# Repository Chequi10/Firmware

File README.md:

# Firmware
Tendra la funcion de controlar los 2 canales CAN, y se comunicara con la pc mendiente puerto Serie

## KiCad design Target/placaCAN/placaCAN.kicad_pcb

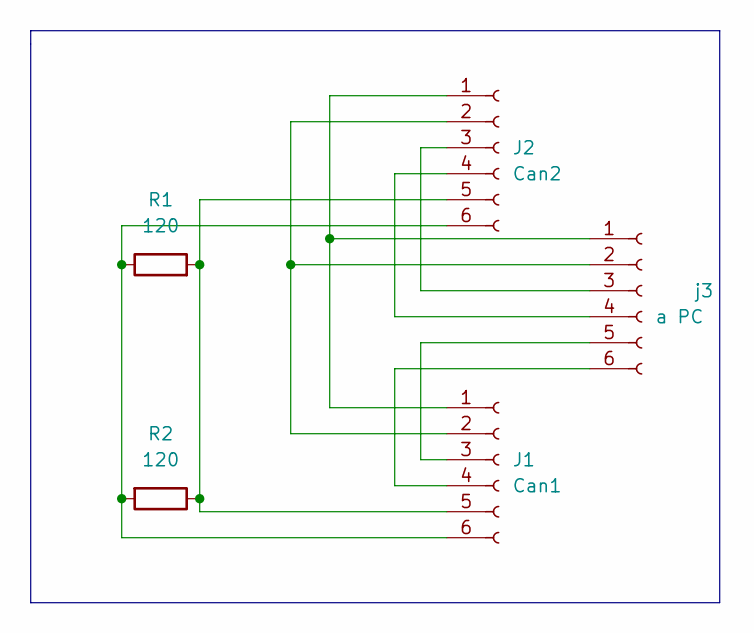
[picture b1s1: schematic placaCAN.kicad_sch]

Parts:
J1: Can1; R_Array_SIP6
J2: Can2; R_Array_SIP6
R1, R2: 120; R_Box_L13.0mm_W4.0mm_P9.00mm
j3: a PC; R_Array_SIP6

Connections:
unnamed: J1.1, J2.1, j3.1
unnamed: J1.2, J2.2, j3.2
unnamed: J1.3, j3.5
unnamed: J1.4, j3.6
unnamed: J1.5, J2.5, R1.2, R2.1
unnamed: J1.6, J2.6, R1.1, R2.2
unnamed: J2.3, j3.3
unnamed: J2.4, j3.4

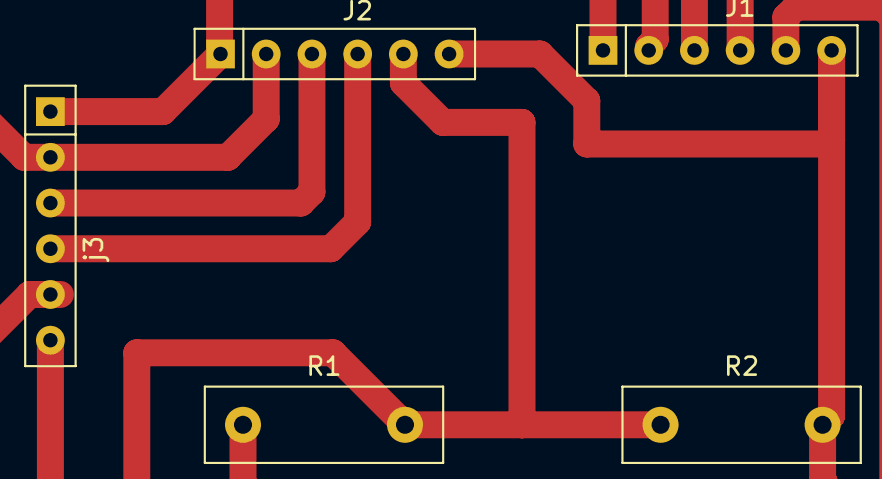
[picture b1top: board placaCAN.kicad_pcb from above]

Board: 2 copper layers, 5 parts (0 on the bottom side), 8 nets.

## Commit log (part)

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2022-05-04 primeros pasos
2022-05-05 probando CAN
2022-11-25 basico
2023-01-17 subiendo
2023-01-20 mas pruebas
2023-01-20 probando
2023-01-20 probando 2
2023-01-20 probando 3
2023-01-21 probando 4
2023-01-21 probando 5
2023-01-21 probando 6
2023-01-21 probando 7
2023-01-21 probando 8
2023-01-21 probando 9
2023-01-22 probando 10
2023-01-22 probando 11
2023-01-22 probando 12
2023-01-22 probando 13
2023-01-26 probando 14
2023-01-26 probando 15
2023-01-28 probando 16
2023-01-28 probando 18
2023-01-29 probando 19
2023-02-02 subiendo 19
2023-02-02 subiendo 20
2023-02-02 subiendo 21
2023-02-02 subiendo 23
2023-02-02 subiendo 22
2023-02-02 subiendo 24
2023-02-13 subiendo 25
2023-02-13 subiendo 26
2023-02-13 subiendo 27
2023-02-13 subiendo 28
2023-02-13 subiendo 29
2023-02-13 subiendo 30
2023-02-17 subiendo 31
2023-02-17 subiendo 32
2023-02-21 char
2023-02-21 sprint
2023-09-22 modificando
2023-09-28 write_some
2023-09-28 envio pulsando tecla
2023-09-28 envio pulsando tecla y opcode
2023-10-05 interrupcion y cola
2023-10-05 rtos interrup y semaforo
2023-10-06 semafor mas time
2023-10-08 co rtos
2023-10-08 con rtos
2023-10-08 con rtos 2
2023-10-10 interface
2023-10-13 protocol
2023-10-14 opcode
2023-10-19 mejoras
2023-10-21 mas mejoras
2023-10-24 last version
2023-12-12 hilos great
2024-02-15 modificado 150224
2024-02-18 host2
2024-04-21 actualizo
